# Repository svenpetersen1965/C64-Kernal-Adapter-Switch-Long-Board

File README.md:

# C64-Kernal-Adapter-Switch-Long-Board
This is a Kernal Adapter/Switch for the Commodore C64 long board prior to ASSY250469. 
The kernal selection can be configured with jumpers, a switch or even with a micro controller. +5V are provided on the pin header 
for this purpose.

This adapter is also suitable for the 1541 Floppy Disk ROM.

This development was inspired by Adrian Black's youtube video <a href="https://youtu.be/GPq5xnJRw2w">How-To: C64 Arduino based Restore Key/Four Kernal Switcher/Hard Reset</a>

# Rev. 2
This board revision provides and optional pin header with the address bits A5 and A8 for stereo SID application.

# Calculation of the BOM prices
The component prices of the BOM 0.0 were summed up. The total is 3.81€, which does not include and shipping fees.

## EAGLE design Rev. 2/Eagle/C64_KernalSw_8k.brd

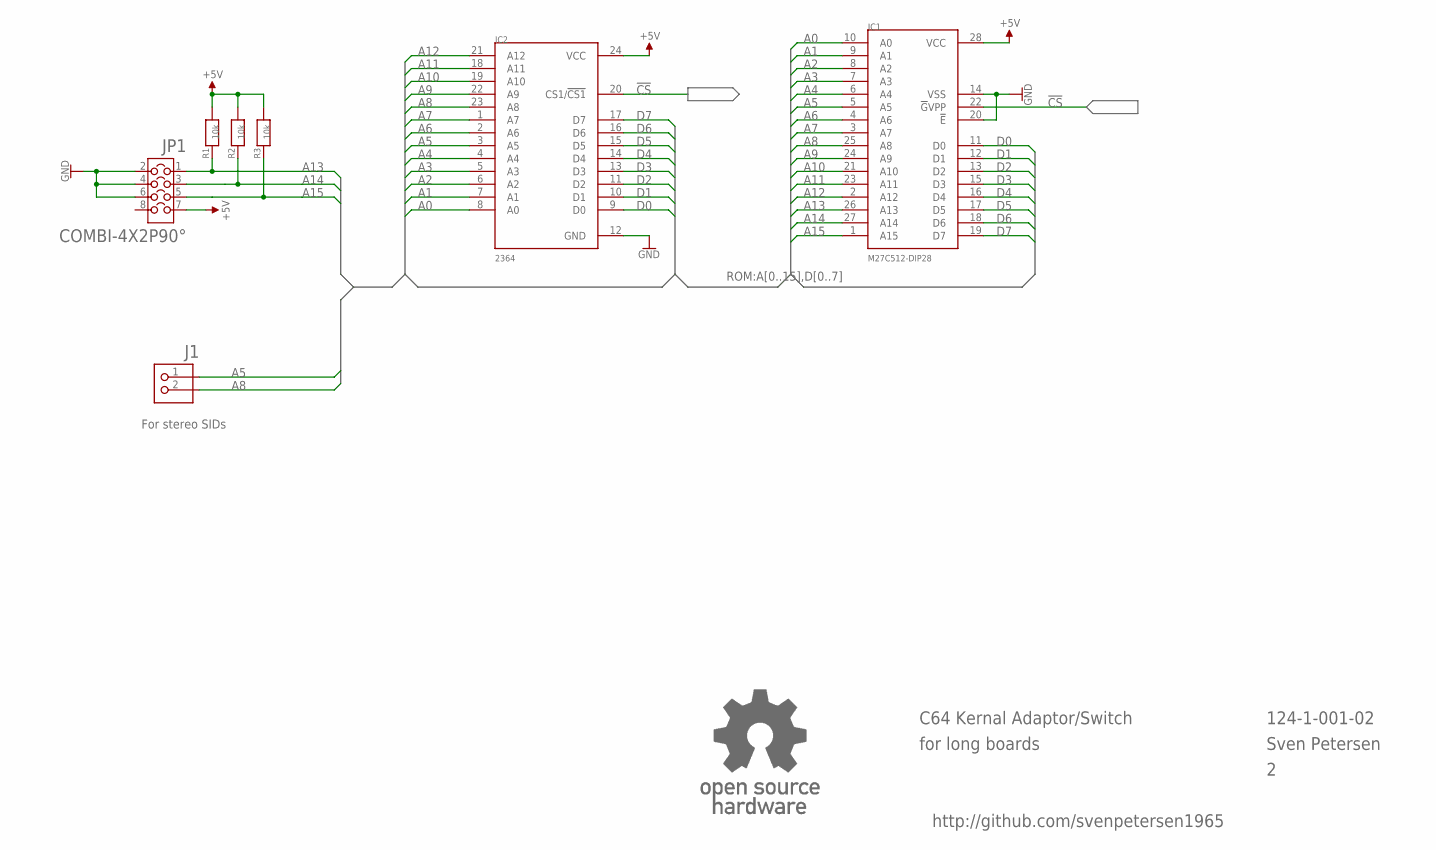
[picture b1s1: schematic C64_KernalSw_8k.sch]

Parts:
IC1: M27C512-DIP28; DIL28-6
IC2: 2364; DIL24_SOCKET
J1: PINHD-1X2; 1X02
JP1: COMBI-4X2P90°; COMBI-4X2-90
R1, R2, R3: 10k; 0805
U$11: OPEN_SOURCE_HW; OPENHW

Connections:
!CS: IC1.22 (!G!VPP), IC2.20 (CS1/!CS1)
+5V: IC1.28 (VCC), IC2.24 (VCC), JP1.7, R1.2, R2.2, R3.2
A0: IC1.10 (A0), IC2.8 (A0)
A1: IC1.9 (A1), IC2.7 (A1)
A2: IC1.8 (A2), IC2.6 (A2)
A3: IC1.7 (A3), IC2.5 (A3)
A4: IC1.6 (A4), IC2.4 (A4)
A5: IC1.5 (A5), IC2.3 (A5), J1.1
A6: IC1.4 (A6), IC2.2 (A6)
A7: IC1.3 (A7), IC2.1 (A7)
A8: IC1.25 (A8), IC2.23 (A8), J1.2
A9: IC1.24 (A9), IC2.22 (A9)
A10: IC1.21 (A10), IC2.19 (A10)
A11: IC1.23 (A11), IC2.18 (A11)
A12: IC1.2 (A12), IC2.21 (A12)
A13: IC1.26 (A13), JP1.1, R1.1
A14: IC1.27 (A14), JP1.3, R2.1
A15: IC1.1 (A15), JP1.5, R3.1
D0: IC1.11 (D0), IC2.9 (D0)
D1: IC1.12 (D1), IC2.10 (D1)
D2: IC1.13 (D2), IC2.11 (D2)
D3: IC1.15 (D3), IC2.13 (D3)
D4: IC1.16 (D4), IC2.14 (D4)
D5: IC1.17 (D5), IC2.15 (D5)
D6: IC1.18 (D6), IC2.16 (D6)
D7: IC1.19 (D7), IC2.17 (D7)
GND: IC1.14 (VSS), IC1.20 (!E), IC2.12 (GND), JP1.2, JP1.4, JP1.6

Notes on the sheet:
124-1-001-02
Sven Petersen
C64 Kernal Adaptor/Switch
for long boards
http://github.com/svenpetersen1965
For stereo SIDs

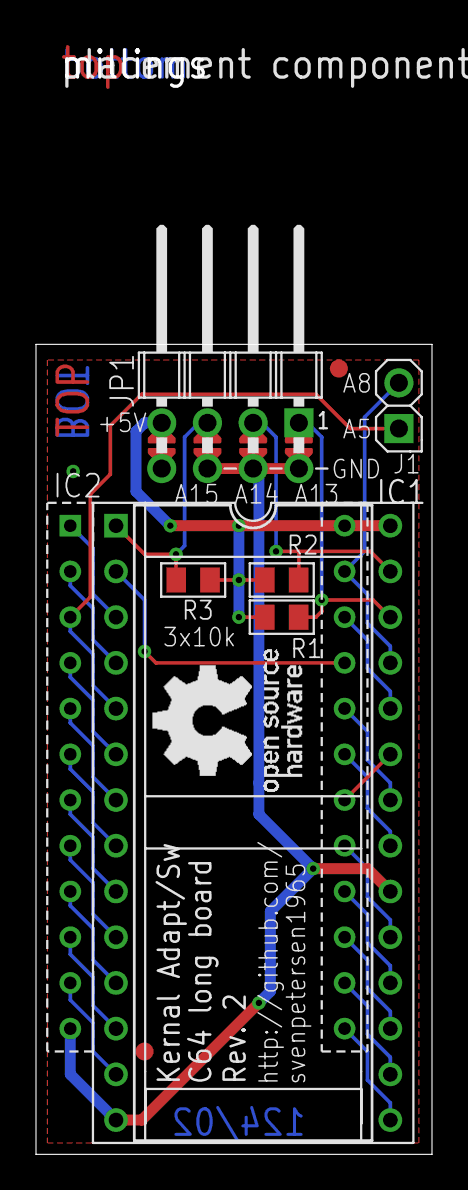
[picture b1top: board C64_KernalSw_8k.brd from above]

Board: 2 copper layers, 22.0 x 45.0 mm, 14 parts (1 on the bottom side), 27 nets.

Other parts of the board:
U$6: SVEN_TAG
U$16: GS28P
U$17, U$18: SMD_REF_R1MM
U$19: 2LAYER
U$20: PCB-TITLE/

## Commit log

2019-05-29 Create LICENSE
2020-06-09 BOM calculation added
2020-08-07 Silk Screen Update
2020-08-16 picknplace in mm and inch
2022-02-25 Rev. 1 released
2022-02-25 Rev. 2 released
